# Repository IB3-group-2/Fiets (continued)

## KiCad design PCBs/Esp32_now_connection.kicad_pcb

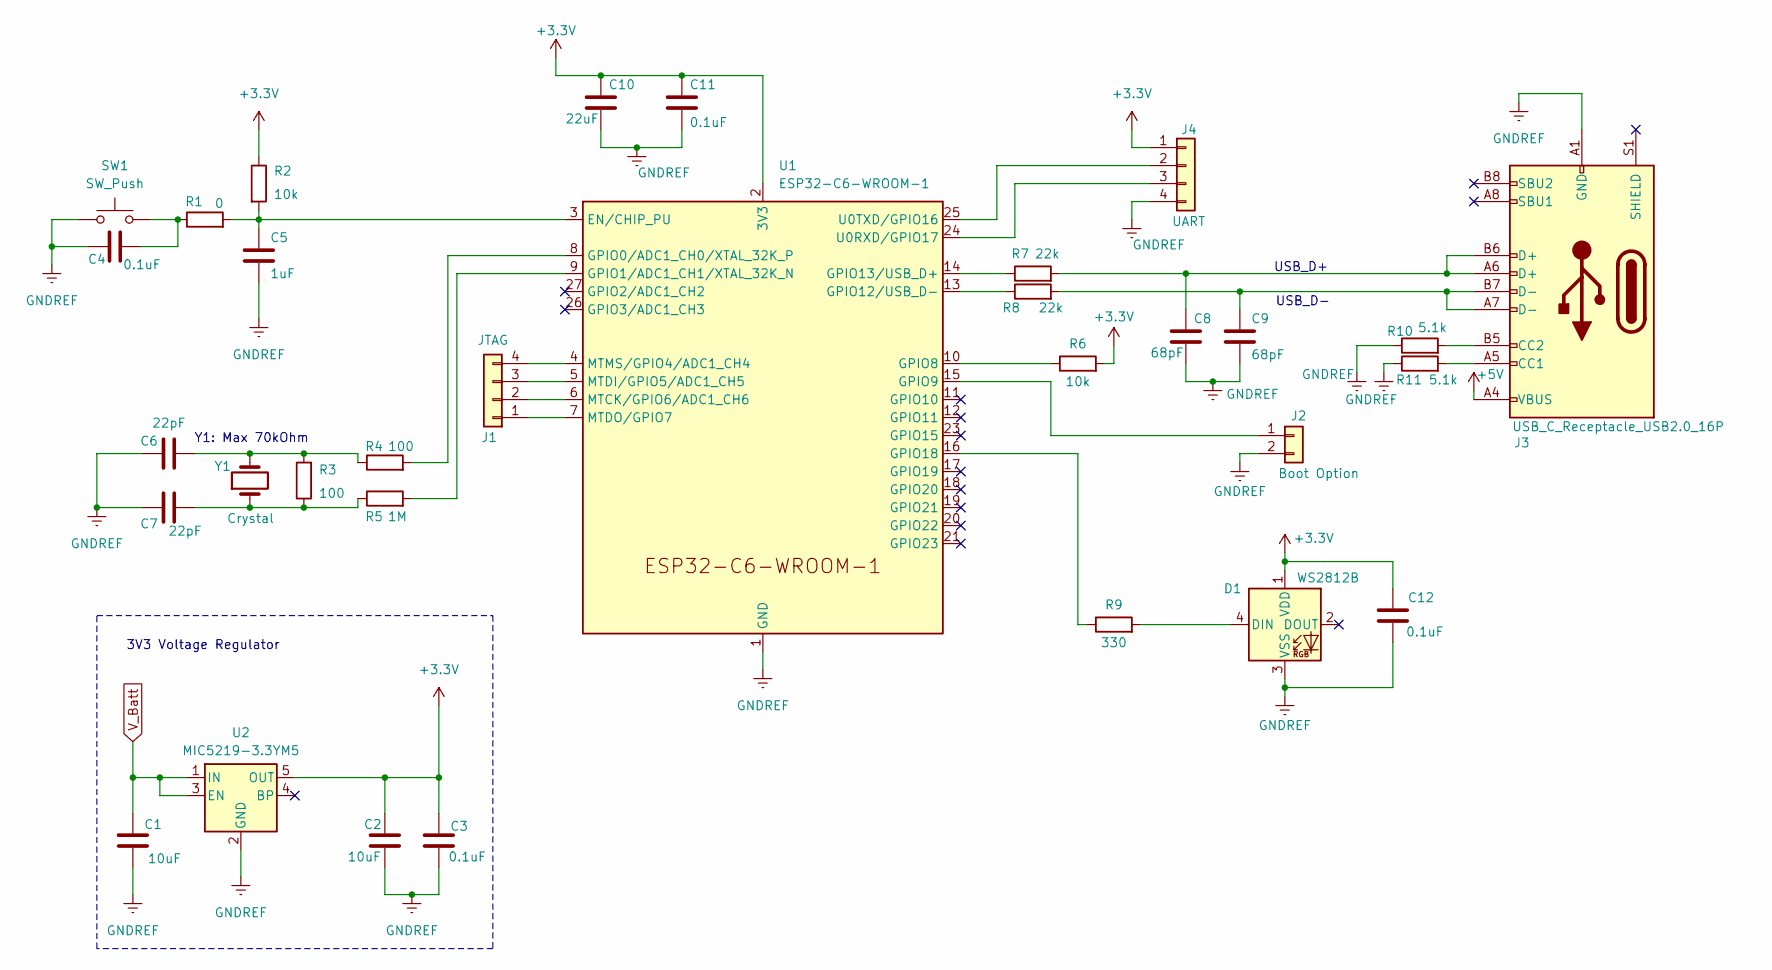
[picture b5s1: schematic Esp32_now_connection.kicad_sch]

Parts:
C1, C2: 10uF; C_0805_2012Metric_Pad1.18x1.45mm_HandSolder
C3, C4, C11, C12: 0.1uF; C_0805_2012Metric_Pad1.18x1.45mm_HandSolder
C5: 1uF; C_0805_2012Metric_Pad1.18x1.45mm_HandSolder
C6, C7: 22pF; C_0805_2012Metric_Pad1.18x1.45mm_HandSolder
C8, C9: 68pF; C_0805_2012Metric_Pad1.18x1.45mm_HandSolder
C10: 22uF; C_0805_2012Metric_Pad1.18x1.45mm_HandSolder
D1: WS2812B; LED_WS2812B_PLCC4_5.0x5.0mm_P3.2mm
J1: JTAG; PinHeader_1x05_P2.54mm_Vertical
J2: Boot Option; PinHeader_1x02_P2.54mm_Vertical
J3: USB_C_Receptacle_USB2.0_16P; USB_C_Receptacle_HRO_TYPE-C-31-M-12
J4: UART; PinHeader_1x04_P2.54mm_Vertical
R1: 0; R_1206_3216Metric_Pad1.30x1.75mm_HandSolder
R2, R6: 10k; R_1206_3216Metric_Pad1.30x1.75mm_HandSolder
R3, R4: 100; R_1206_3216Metric_Pad1.30x1.75mm_HandSolder
R5: 1M; R_1206_3216Metric_Pad1.30x1.75mm_HandSolder
R7, R8: 22k; R_1206_3216Metric_Pad1.30x1.75mm_HandSolder
R9: 330; R_1206_3216Metric_Pad1.30x1.75mm_HandSolder
R10, R11: 5.1k; R_1206_3216Metric_Pad1.30x1.75mm_HandSolder
SW1: SW_Push; Panasonic_EVQPUJ_EVQPUA
U1: ESP32-C6-WROOM-1
U2: MIC5219-3.3YM5; SOT-23-5
Y1: Crystal; Crystal_SMD_3215-2Pin_3.2x1.5mm

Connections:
+3.3V: C2.1, C3.1, C10.2, C11.2, C12.1, D1.1 (VDD), J4.1, R2.1, R6.2, U1.2 (3V3), U2.5 (OUT)
+5V: J3.A4 (VBUS), J3.A9 (VBUS), J3.B4 (VBUS), J3.B9 (VBUS)
GNDREF: C1.2, C2.2, C3.2, C4.2, C5.1, C6.1, C7.1, C8.1, C9.1, C10.1, C11.1, C12.2, D1.3 (VSS), J2.2, J3.A1 (GND), J3.A12 (GND), J3.B1 (GND), J3.B12 (GND), J4.4, R10.1, R11.1, SW1.1, U1.1 (GND), U1.28 (GND), U1.29 (GND), U2.2 (GND)
unnamed: C4.1, R1.1, SW1.2
unnamed: C6.2, R3.2, R4.1, Y1.2
unnamed: C7.2, R3.1, R5.1, Y1.1
unnamed: C8.2, J3.A6 (D+), J3.B6 (D+), R7.2
unnamed: C9.2, J3.A7 (D-), J3.B7 (D-), R8.2
unnamed: D1.4 (DIN), R9.2
unnamed: J1.1, U1.7 (MTDO/GPIO7)
unnamed: J1.2, U1.6 (MTCK/GPIO6/ADC1_CH6)
unnamed: J1.3, U1.5 (MTDI/GPIO5/ADC1_CH5)
unnamed: J1.4, U1.4 (MTMS/GPIO4/ADC1_CH4)
unnamed: J2.1, U1.15 (GPIO9)
unnamed: J3.A5 (CC1), R11.2
unnamed: J3.B5 (CC2), R10.2
unnamed: J4.2, U1.25 (U0TXD/GPIO16)
unnamed: J4.3, U1.24 (U0RXD/GPIO17)
unnamed: C5.2, R1.2, R2.2, U1.3 (EN/CHIP_PU)
unnamed: R4.2, U1.8 (GPIO0/ADC1_CH0/XTAL_32K_P)
unnamed: R5.2, U1.9 (GPIO1/ADC1_CH1/XTAL_32K_N)
unnamed: R6.1, U1.10 (GPIO8)
unnamed: R8.1, U1.13 (GPIO12/USB_D-)
unnamed: R7.1, U1.14 (GPIO13/USB_D+)
unnamed: R9.1, U1.16 (GPIO18)
V_Batt: C1.1, U2.1 (IN), U2.3 (EN)

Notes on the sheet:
USB_D+
USB_D-
3V3 Voltage Regulator
Y1: Max 70kOhm

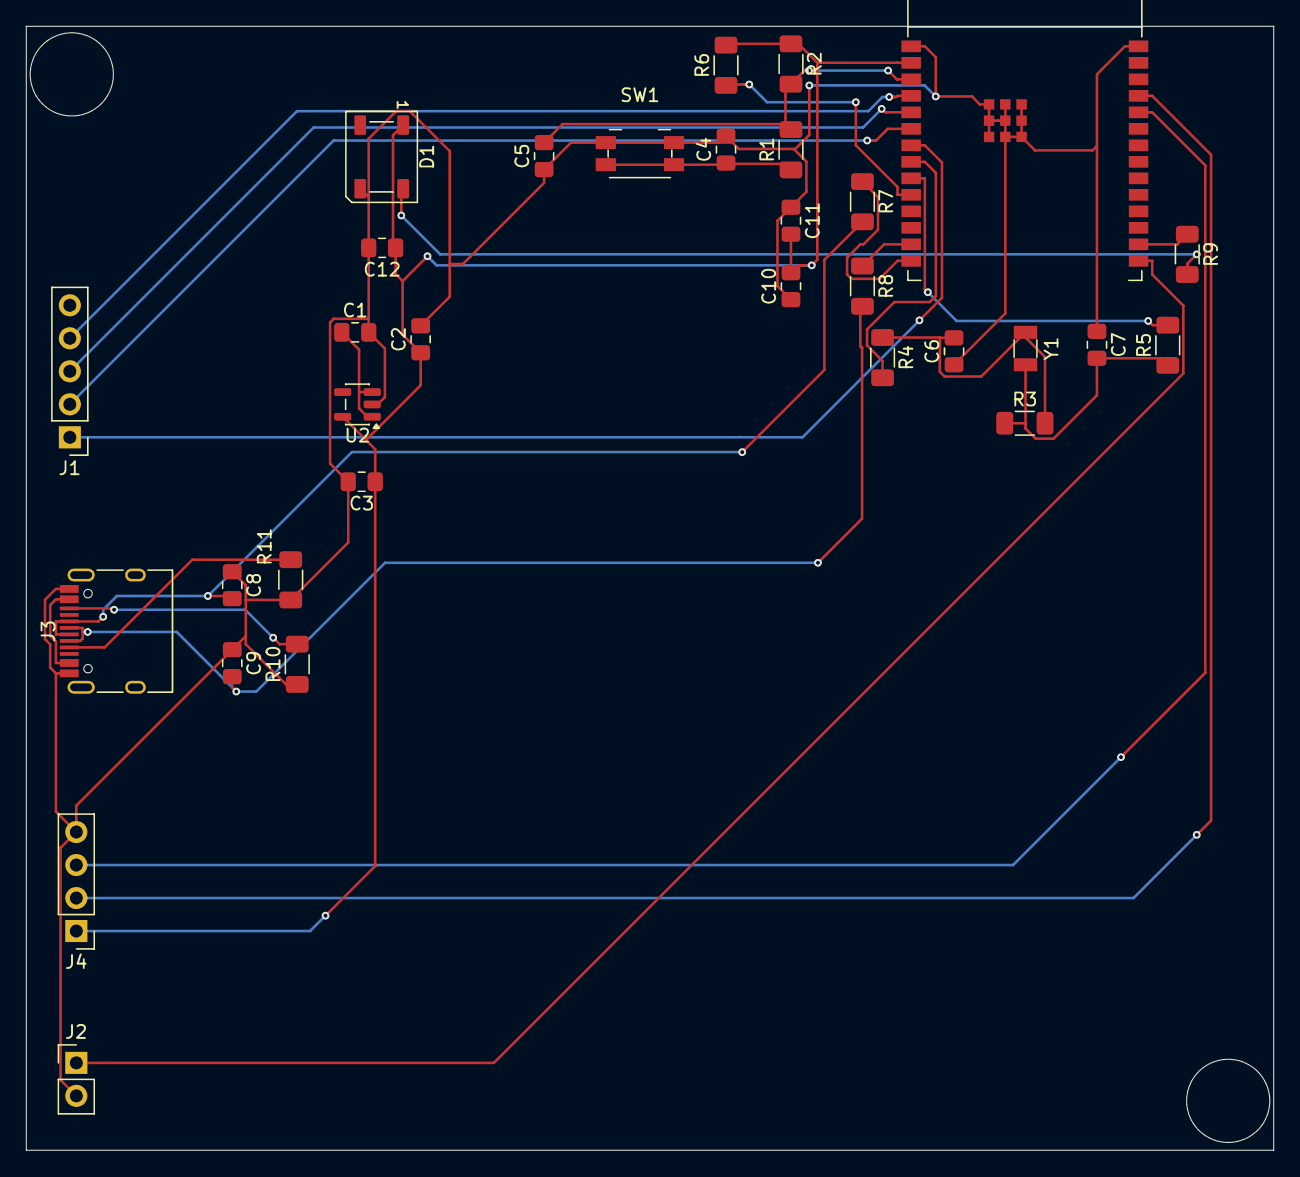
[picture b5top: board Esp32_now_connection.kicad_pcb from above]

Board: 2 copper layers, 96.0 x 86.5 mm, 32 parts (0 on the bottom side), 26 nets.

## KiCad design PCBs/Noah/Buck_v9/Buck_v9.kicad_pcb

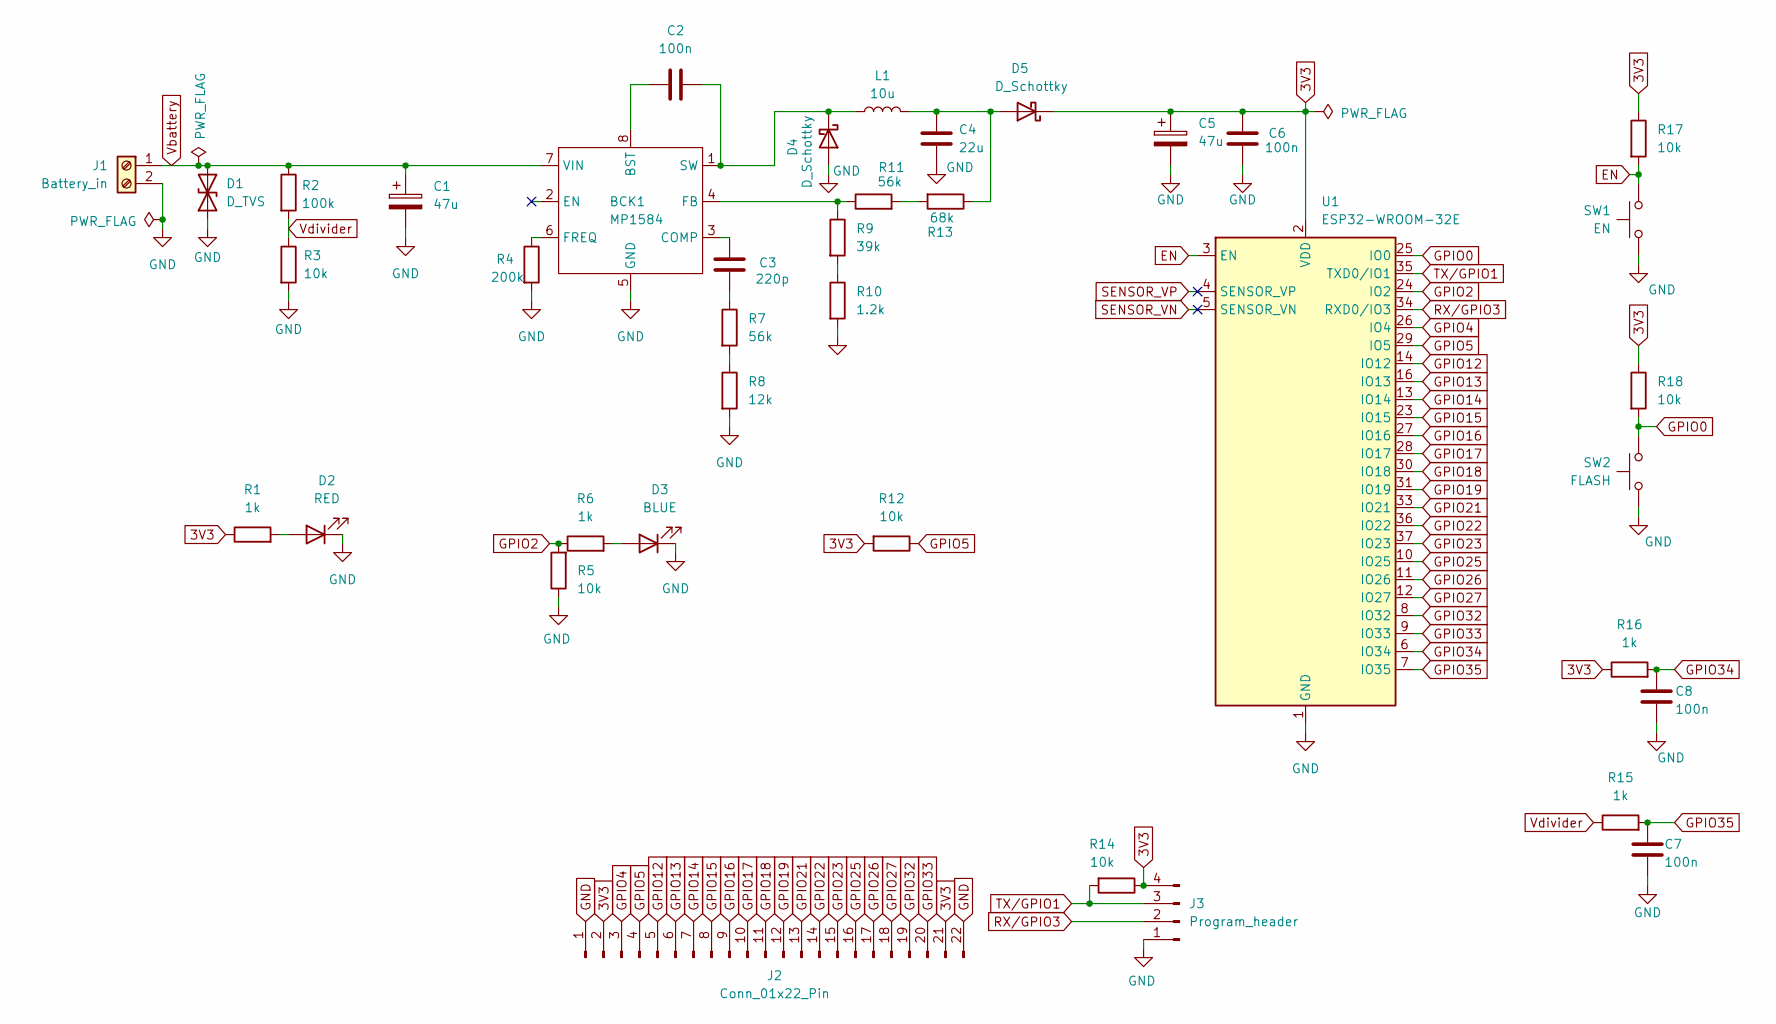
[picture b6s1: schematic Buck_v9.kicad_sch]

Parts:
BCK1: MP1584; SOIC-8-1EP_3.9x4.9mm_P1.27mm_EP2.29x3mm_ThermalVias
C1, C5: 47u; CP_Elec_6.3x5.4
C2, C6, C7, C8: 100n; C_1206_3216Metric_Pad1.33x1.80mm_HandSolder
C3: 220p; C_1206_3216Metric_Pad1.33x1.80mm_HandSolder
C4: 22u; C_1210_3225Metric_Pad1.33x2.70mm_HandSolder
D1: D_TVS; D_SMB-SMC_Universal_Handsoldering
D2: RED; LED_0805_2012Metric_Pad1.15x1.40mm_HandSolder
D3: BLUE; LED_0805_2012Metric_Pad1.15x1.40mm_HandSolder
D4, D5: D_Schottky; D_SMC-RM10_Universal_Handsoldering
J1: Battery_in; TerminalBlock_MaiXu_MX126-5.0-02P_1x02_P5.00mm
J2: Conn_01x22_Pin; PinHeader_1x22_P2.54mm_Vertical
J3: Program_header; PinHeader_1x04_P2.54mm_Vertical
L1: 10u; L_Wurth_WE-LQSH-3012
R1, R6, R15, R16: 1k; R_1206_3216Metric_Pad1.30x1.75mm_HandSolder
R2: 100k; R_1206_3216Metric_Pad1.30x1.75mm_HandSolder
R3, R5, R12, R14, R17, R18: 10k; R_1206_3216Metric_Pad1.30x1.75mm_HandSolder
R4: 200k; R_1206_3216Metric_Pad1.30x1.75mm_HandSolder
R7, R11: 56k; R_1206_3216Metric_Pad1.30x1.75mm_HandSolder
R8: 12k; R_1206_3216Metric_Pad1.30x1.75mm_HandSolder
R9: 39k; R_1206_3216Metric_Pad1.30x1.75mm_HandSolder
R10: 1.2k; R_1206_3216Metric_Pad1.30x1.75mm_HandSolder
R13: 68k; R_1206_3216Metric_Pad1.30x1.75mm_HandSolder
SW1: EN; SW_Tactile_SPST_NO_Straight_CK_PTS636Sx25SMTRLFS
SW2: FLASH; SW_Tactile_SPST_NO_Straight_CK_PTS636Sx25SMTRLFS
U1: ESP32-WROOM-32E

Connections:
3V3: C5.1, C6.1, D5.1 (K), J2.2, J2.21, J3.4, R1.1, R12.2, R14.1, R16.1, R17.1, R18.1, U1.2 (VDD)
EN: R17.2, SW1.1, U1.3 (EN)
GND: BCK1.5 (GND), C1.2, C4.2, C5.2, C6.2, C7.2, C8.2, D1.1 (A1), D2.1 (K), D3.1 (K), D4.2 (A), J1.2, J2.1, J2.22, J3.1, R3.2, R4.2, R5.1, R8.2, R10.2, SW1.2, SW2.2, U1.1 (GND), U1.15 (GND), U1.38 (GND), U1.39 (GND)
GPIO0: R18.2, SW2.1, U1.25 (IO0)
GPIO2: R5.2, R6.1, U1.24 (IO2)
GPIO4: J2.3, U1.26 (IO4)
GPIO5: J2.4, R12.1, U1.29 (IO5)
GPIO12: J2.5, U1.14 (IO12)
GPIO13: J2.6, U1.16 (IO13)
GPIO14: J2.7, U1.13 (IO14)
GPIO15: J2.8, U1.23 (IO15)
GPIO16: J2.9, U1.27 (IO16)
GPIO17: J2.10, U1.28 (IO17)
GPIO18: J2.11, U1.30 (IO18)
GPIO19: J2.12, U1.31 (IO19)
GPIO21: J2.13, U1.33 (IO21)
GPIO22: J2.14, U1.36 (IO22)
GPIO23: J2.15, U1.37 (IO23)
GPIO25: J2.16, U1.10 (IO25)
GPIO26: J2.17, U1.11 (IO26)
GPIO27: J2.18, U1.12 (IO27)
GPIO32: J2.19, U1.8 (IO32)
GPIO33: J2.20, U1.9 (IO33)
GPIO34: C8.1, R16.2, U1.6 (IO34)
GPIO35: C7.1, R15.2, U1.7 (IO35)
unnamed: BCK1.8 (BST), C2.1
unnamed: BCK1.3 (COMP), C3.1
unnamed: BCK1.4 (FB), R9.1, R11.1
unnamed: BCK1.6 (FREQ), R4.1
unnamed: BCK1.1 (SW), C2.2, D4.1 (K), L1.1
unnamed: C3.2, R7.1
unnamed: D2.2 (A), R1.2
unnamed: D3.2 (A), R6.2
unnamed: C4.1, D5.2 (A), L1.2, R13.1
unnamed: R7.2, R8.1
unnamed: R9.2, R10.1
unnamed: R11.2, R13.2
RX/GPIO3: J3.2, U1.34 (RXD0/IO3)
SENSOR_VN: U1.5 (SENSOR_VN)
SENSOR_VP: U1.4 (SENSOR_VP)
TX/GPIO1: J3.3, R14.2, U1.35 (TXD0/IO1)
Vbattery: BCK1.7 (VIN), C1.1, D1.2 (A2), J1.1, R2.1
Vdivider: R2.2, R3.1, R15.1

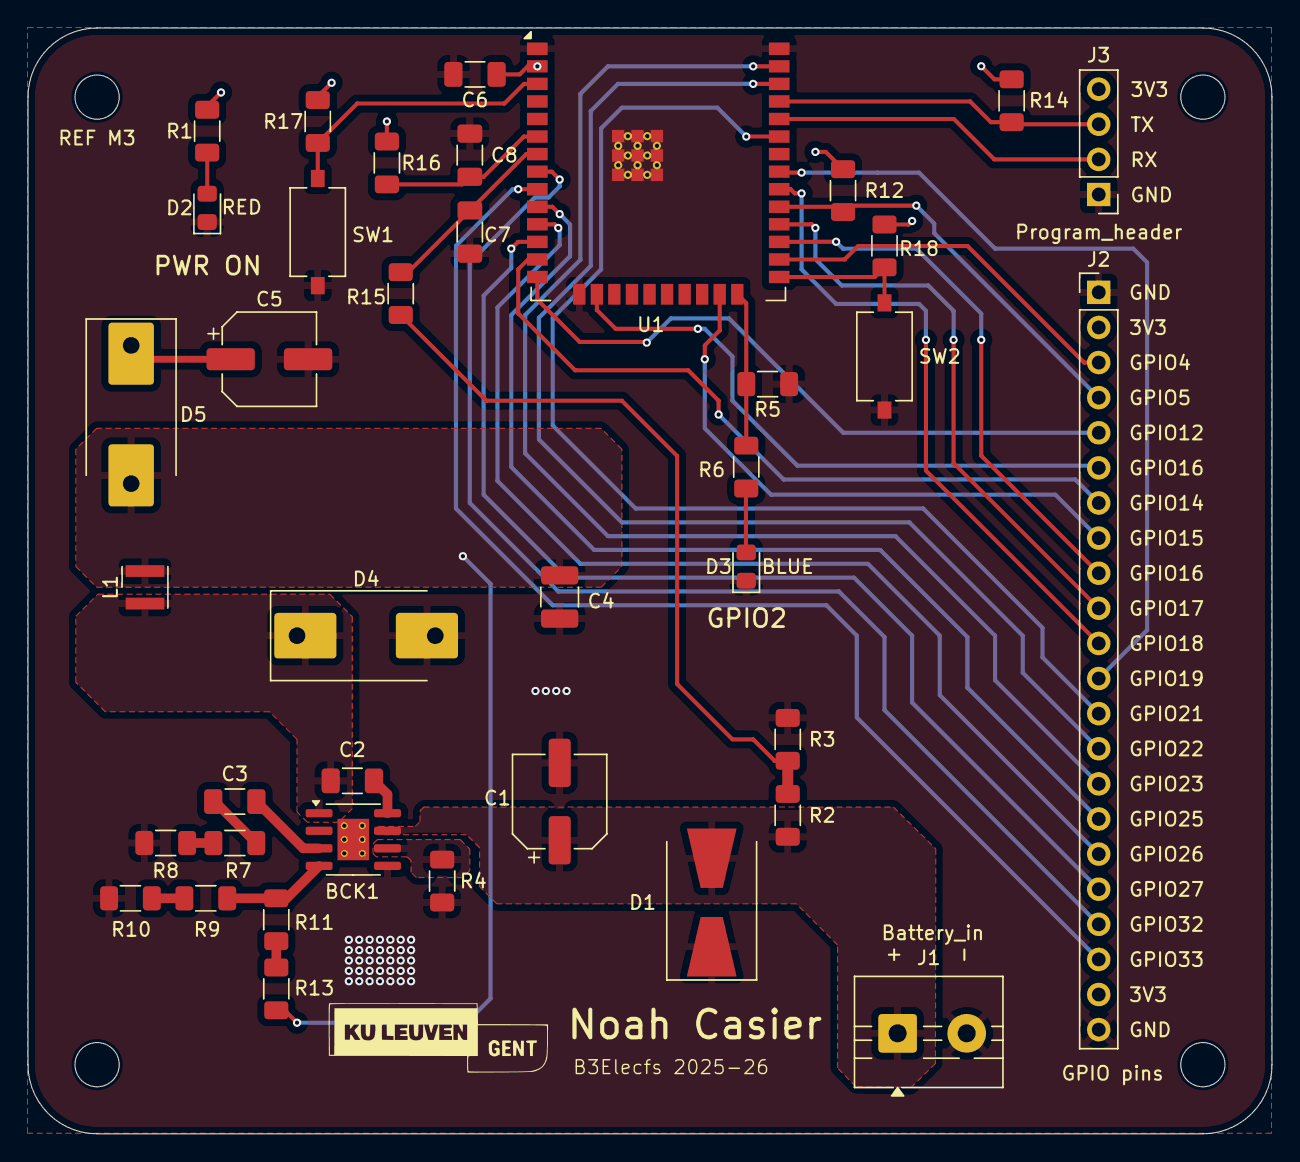
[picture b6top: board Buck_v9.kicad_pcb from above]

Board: 2 copper layers, 90.0 x 80.0 mm, 40 parts (0 on the bottom side), 41 nets.

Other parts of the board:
REF M3: MountingHole_3.2mm_M3

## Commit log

2025-10-16 start BuckLars schematic
2025-10-21 Create BT master connection
2025-10-22 added buck converter to schematic
2025-10-22 cleanup chematic and assinged footprints
2025-10-23 added buck converters schematic
2025-10-24 wired buck converter pcb
2025-10-25 upload pcb remote estop
    mijn kicad project voor de pcb die dus als remote stop knop zal werken
2025-10-26 layout changes schematic
2025-10-28 changed footprints buck
2025-10-31 Upload pcb
2025-11-02 pcb remote estop v1
    eerste versie van pcb met slechte routing
2025-11-02 wired second buck converter
2025-11-04 added 5V buck
2025-11-04 pcb remote estop v2
    Versie 2 met betere routing en begin van de silkscreen
2025-11-04 pcb remote estop v2
    pcb Voldoet nu aan de DRC met slechts 1 warning namelijk dat esp footprint niet meer overeen komt met de library doordat de via grootte moest worden aangepast.
2025-11-05 added qr code and status leds
2025-11-08 Add new PCB
    Added newest version of my PCB
2025-11-08 pcb remote estop v3
    kleine fout met marges voor knoppen gefixd drc is nu ook opnieuw goed
2025-11-09 Remote_Control_Maxime de Ryckel
2025-11-09 Maxime_ESP_Remote
2025-11-10 pcb_Quinten
2025-11-10 generated gerbers
2025-11-12 changed buck driver circuit
2025-11-14 pcb remote estop v4
    finale versie volledig in orde me de commentaren van de prof
2025-12-08 added code folder with first code
2025-12-08 first pwm code for buck
2025-12-08 now test code for buck driver
2025-12-11 CODE: first succes buck driver
2025-12-11 CODE: 100khz switching, adjustable pwm
2025-12-13 changed supply of gate driver
2025-12-13 render van de fiets
    fiets is gerenderd blend file toegevoegd voor verdere aanpassingen
2025-12-15 enabled second buck and read oupout voltages
2026-03-24 added blcd and pid sensor files
2026-03-24 added the real files
